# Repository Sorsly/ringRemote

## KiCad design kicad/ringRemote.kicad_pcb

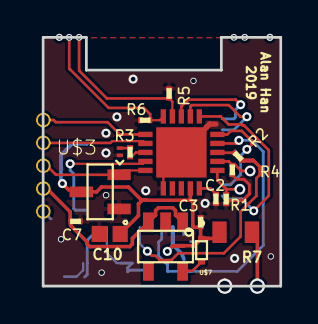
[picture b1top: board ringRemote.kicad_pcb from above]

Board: 4 copper layers, 13.2 x 13.8 mm, 23 parts (0 on the bottom side), 24 nets.

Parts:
C2, C3, C7: 1uF; 0201
C4: 0.1uF; 0201
C5, C6: 4pF; 0201
C9, C10: 10uF; 0402
D1: ORANGE; LED-0201
R1, R2, R3, R4, R5, R6: 100k; 0201
R7: 1.8k; 0805
U$1: MAX32660; T2044+5C
U$2: ATBTLC1000-ZR110CA
U$3: TPS3839G25; 3-SOT-23
U$4: TLV700; SOT-23-THIN
U$6: 1X5_1.27MM
U$7: DB2731400L; SSSMINI2
Y1: 32.768kHz; CRYSTAL-SMD-3.2X1.5MM

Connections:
+5V: C7.1, U$4.P$1, U$4.P$3, U$6.P$2
/AO_GPIO_0_WAKE: U$1.P$4, U$2.P$1
/BT_CTS: U$1.P$15, U$2.P$20
/BT_RTS: U$1.P$16, U$2.P$21
/BT_RXD: U$1.P$18, U$2.P$14
/BT_TXD: U$1.P$17, U$2.P$15
/CLKSRC: C6.1, U$2.P$33, Y1.P$1
/C_EN: R2.2, U$1.P$13
/MAXRST: U$1.P$5, U$3.P$2, U$6.P$3
/PB1: R1.1, U$1.P$11
/PB2: R4.1, U$1.P$12
/PB3: R5.1, U$1.P$19
/PB4: R6.1, U$1.P$20
/SWDCLK: U$1.P$1, U$6.P$5
/SWDIO: U$1.P$2, U$6.P$4
/WAKEMONITOR: U$1.P$14, U$2.P$28
GND: C2.2, C3.2, C4.2, C5.2, C6.2, C7.2, C9.2, C10.2, D1.C, R1.2, R4.2, R5.2, R6.2, U$1.P$0, U$1.P$6, U$2.P$11, U$2.P$26, U$2.P$35, U$3.P$1, U$4.P$2, U$6.P$1
unnamed: C2.1, U$1.P$10
unnamed: C5.1, U$2.P$34, Y1.P$2
unnamed: D1.A, R3.2
unnamed: R2.1, U$2.P$30
unnamed: R3.1, U$1.P$3
unnamed: U$4.P$5, U$7.P$2
VCC: C3.1, C4.1, C9.1, C10.1, R7.2, U$1.P$9, U$2.P$7, U$2.P$27, U$3.P$3, U$7.P$1

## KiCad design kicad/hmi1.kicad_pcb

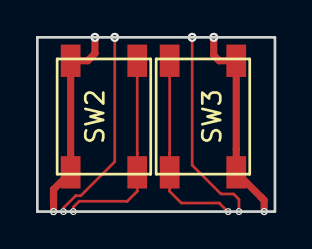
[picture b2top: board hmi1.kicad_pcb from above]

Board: 2 copper layers, 13.2 x 9.7 mm, 3 parts (0 on the bottom side), 3 nets.

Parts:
FRAME1: FRAME-LETTERNO_PACKAGE; DUMMY
SW2, SW3: SW_SPST_0; RS-187R05A2-DS MT RT

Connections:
/PB2: SW3.1, SW3.2
/PB3: SW2.1, SW2.2
VCC: SW2.3, SW2.4, SW3.3, SW3.4

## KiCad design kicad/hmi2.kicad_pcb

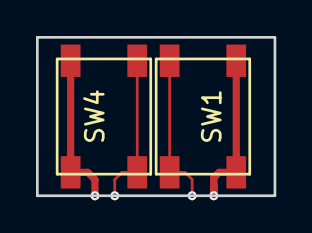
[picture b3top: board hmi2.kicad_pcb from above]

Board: 2 copper layers, 13.2 x 8.8 mm, 3 parts (0 on the bottom side), 3 nets.

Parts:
FRAME1: FRAME-LETTERNO_PACKAGE; DUMMY
SW1, SW4: SW_SPST_0; RS-187R05A2-DS MT RT

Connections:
/PB1: SW1.1, SW1.2
/PB4: SW4.1, SW4.2
VCC: SW1.3, SW1.4, SW4.3, SW4.4

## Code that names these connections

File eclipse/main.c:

/**
 * @file    main.c
 * @brief   Hello World!
 * @details This example uses the UART to print to a terminal and flashes an LED.
 */

/*******************************************************************************
 * Copyright (C) 2016 Maxim Integrated Products, Inc., All Rights Reserved.
 *
 * Permission is hereby granted, free of charge, to any person obtaining a
 * copy of this software and associated documentation files (the "Software"),
 * to deal in the Software without restriction, including without limitation
 * the rights to use, copy, modify, merge, publish, distribute, sub-license,
 * and/or sell copies of the Software, and to permit persons to whom the
 * Software is furnished to do so, subject to the following conditions:
 *
 * The above copyright notice and this permission notice shall be included
 * in all copies or substantial portions of the Software.
 *
 * THE SOFTWARE IS PROVIDED "AS IS", WITHOUT WARRANTY OF ANY KIND, EXPRESS
 * OR IMPLIED, INCLUDING BUT NOT LIMITED TO THE WARRANTIES OF
 * MERCHANTABILITY, FITNESS FOR A PARTICULAR PURPOSE AND NONINFRINGEMENT.
 * IN NO EVENT SHALL MAXIM INTEGRATED BE LIABLE FOR ANY CLAIM, DAMAGES
 * OR OTHER LIABILITY, WHETHER IN AN ACTION OF CONTRACT, TORT OR OTHERWISE,
 * ARISING FROM, OUT OF OR IN CONNECTION WITH THE SOFTWARE OR THE USE OR
 * OTHER DEALINGS IN THE SOFTWARE.
 *
 * Except as contained in this notice, the name of Maxim Integrated
 * Products, Inc. shall not be used except as stated in the Maxim Integrated
 * Products, Inc. Branding Policy.
 *
 * The mere transfer of this software does not imply any licenses
 * of trade secrets, proprietary technology, copyrights, patents,
 * trademarks, mask work rights, or any other form of intellectual
 * property whatsoever. Maxim Integrated Products, Inc. retains all
 * ownership rights.
 *
 * $Date: 2018-08-09 23:45:02 +0000 (Thursday, 09 August 2018) $
 * $Revision: 36818 $
 *
 ******************************************************************************/

/***** Includes *****/
#include <stdio.h>
#include <stdint.h>
#include <stdbool.h>

//delay libraries
#include "mxc_config.h"
#include "mxc_delay.h"

#include "tmr.h"
#include "tmr_utils.h"

//led library
#include "led.h"

//required libraries
#include "board.h"  //this NEEDS to be before gpio.h apparently
#include "gpio.h"


/***** Definitions *****/
//reminder that all pins listed here are SOFTWARE, not HARDWARE
#define PB1_PIN     PIN_9
#define PB2_PIN     PIN_8
#define PB3_PIN     PIN_3
#define PB4_PIN     PIN_2
#define THRESH      10      //ms
#define TMR0        MXC_TMR0

/***** Globals *****/

/***** Functions *****/

bool debounce(bool *prevSt, int *tStart, bool currSt) {
    if(currSt != *prevSt) {     //change has occured
        TMR_Enable(TMR0);       //enables timer on change
        *tStart = TMR_GetCount(TMR0);
        *prevSt = currSt;
    } else {
        if((TMR_GetCount(TMR0) - *tStart) > THRESH) {
            *prevSt = currSt;
            currSt = !currSt;
            TMR_Disable(TMR0);  //disables timer after settling
        }
    }

    return currSt;
}

void debounce(bool press) {
    if(press == true) {
        on++;   //count time up
        off = 0;
        if(on > THRESH) {
            if(output == false) {
                //action
                output = true;
            }
        }
    } else {
        off++;
        on = 0;
        if(off > THRESH) {
            output = 0;
            off = 0;
        }
    }
}

//inits atbtlc device
void btInit() {
    //TODO

}

//tells atbtlc to send bytes
void btTx(int byte) {
    //TODO
    
}

//timer interrupt
void gpio_isr(void *cbdata)
{
    //cbdata.ten = 1;   //enable timer
    TMR_Enable(TMR0);   //enable timer
}


int main(void)
{
//declarations
    gpio_cfg_t pb1, pb2, pb3, pb4;
    bool fx1 = false;
    bool fx2 = false;
    bool fx3 = false;
    bool fx4 = false;

    //int tElapsed;

    tmr_cfg_t tmr;

    btInit();

//MXC_TMR0 init config
    /*
    TMR0_CN.ten = 0;    //disable timer
    TMR0_CN.tmode = 000b;    //one-shot mode
    //TMR0_CN.pres3:TMR0_CN.pres    //set prescaler //TODO
    TMR0_CMP = 10;
    //use "TMR0_CN.ten = 1;" to enable timer
    */

    unsigned clk_shift = 0;
    uint64_t max_us;

    /* Find the proper clock shift for timer */
    do {
        max_us = (uint64_t)((0xFFFFFFFFUL / ((uint64_t)PeripheralClock >> clk_shift++)) * 1000000UL);
    } while (us > max_us);
    clk_shift--;

    TMR_Disable(TMR0);
    TMR_Init(TMR0, 0, 0);   //prescaler is second arg
    
    //ms to ticks
    uint32_t ticks; //ticks temp var
    TMR_GetTicks(TMR0, THRESH, TMR_UNIT_MILLISEC, &ticks);  //get ticks from ms
    
    //define tmr
    tmr.mode = TMR_MODE_ONESHOT;
    tmr.cmp_cnt = ticks;    //timer mode?
    tmr.pol = 0;    //compare register value in timer ticks. not used
    
    TMR_Config(TMR0, &tmr); //configure tmr as TMR0

    //use "TMR_Enable(TMR0);" to enable timer


//interrupt pin init (turn into function)TODO
    pb1.port = PORT_0;
    pb1.mask = PB1_PIN;
    pb1.pad = GPIO_PAD_PULL_DOWN;
    pb1.func = GPIO_FUNC_IN;
    GPIO_Config(&pb1);
    
    //GPIO_RegisterCallback(&pb1, gpio_isr, &tElapsed);
    //GPIO_RegisterCallback(&pb1, gpio_isr, &TMR0_CN);
    GPIO_RegisterCallback(&pb1, gpio_isr);
    
    GPIO_IntConfig(&pb1, GPIO_INT_EDGE, GPIO_INT_BOTH); //reads on falling and rising
    
    GPIO_IntEnable(&pb1);
    NVIC_EnableIRQ((IRQn_Type)MXC_GPIO_GET_IRQ(GPIO_PORT_INTERRUPT_IN));

    pb2.port = PORT_0;
    pb2.mask = PB2_PIN;
    pb2.pad = GPIO_PAD_PULL_DOWN;
    pb2.func = GPIO_FUNC_IN;

    pb3.port = PORT_0;
    pb3.mask = PB3_PIN;
    pb3.pad = GPIO_PAD_PULL_DOWN;
    pb3.func = GPIO_FUNC_IN;

    pb4.port = PORT_0;
    pb4.mask = PB4_PIN;
    pb4.pad = GPIO_PAD_PULL_DOWN;
    pb4.func = GPIO_FUNC_IN;

//loop
    while(1) {
        if(TMR_IntStatus(TMR0)) {   //check if TMR0 finished the cnt
            //somehow pass which switch got pushed to the bt func
            if(GPIO_InGet(&pb1)) {
                btTx(1);
            } else if(GPIO_InGet(&pb2)) {
                btTx(2);
            } else if(GPIO_InGet(&pb3)) {
                btTx(3);
            } else if(GPIO_InGet(&pb4)) {
                btTx(4);
            }

            //TMR_IntClear(TMR0);     //unnecessary because interrupt clears auto?
        }
        

        //old code, not oriented for interrupts
        /***
        //read pb1
        if (GPIO_InGet(&pb1)) {
            fx1 = true;
        } else {
            fx1 = false;
        }

        //read pb2
        if (GPIO_InGet(&pb2)) {
            fx2 = true;
        } else {
            fx2 = false;
        }

        //read pb3
        if (GPIO_InGet(&pb3)) {
            fx3 = true;
        } else {
            fx3 = false;
        }

        //read pb4
        if (GPIO_InGet(&pb4)) {
            fx4 = true;
        } else {
            fx4 = false;
        }

        if (fx1 || fx2 || fx3 || fx4) {
            LED_On(0);  //just for the evalboard?
        } else {
            LED_Off(0);
        }
        ***/
    }
}

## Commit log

2019-01-06 added a todo list; did some thinking for the HMI pushbuttons
2019-01-06 added to bom: battery supervisor, charging circuit components; put components on board space to estimate stuff
2019-01-06 moved some datasheets from local/proj
2019-01-06 added battery supervisor part, wired it up
2019-01-07 made a new sheet, moved all power stuff to second sheet; added charger circuit; added connector; added battery. pretty much just need to determine the programming interface before I start doing board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
2019-01-07 some models from octopart
2019-01-07 added pertinent datasheets, including programming stuff for MAX
2019-01-07 misc save
2019-01-14 made rough layout of board; swapped some pins for pushbuttons in sch (to atbtlc); understood programming workflow a bit better (likely using SWD instead of i2c)
2019-01-14 created mech directory
2019-01-16 think I moved the pb's back to MAX32660 (using the i2c lines because they're not needed)
2019-01-19 pretty much finished the board; swapped diode out for a smaller package
2019-01-21 tried to create some vias for the pushbuttons, these need to be routed offboard (past castellated edge near antenna section); created rev1 of mech model (this needs to be bigger and smoother, hurts m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
2019-01-22 moved eagle files to subdir
2019-01-22 some misc mech outputs
2019-01-22 switched over to kicad for 4-layer stuff
2019-01-22 switched over to kicad for 4-layer stuff
    *also fixed some clearance issues (set up some drc stuff)
    *wired out hmi traces towards antenna end
    *redefined board edge.cuts to suit custom shape better
2019-01-22 had to wire GND castellation to polypour; the border technically isn't filled
2019-01-23 finished routing main board; changed programming castellations to circular; created subschematic for battery board
2019-01-23 finished battery board; added switch footprint to library; need to make symbol for switch and make switch board
2019-01-24 added 4 pin spst switch and finished sch
2019-01-24 finished hmi boards
2019-01-24 added pdfs of to-scale layouts (for design review)
2019-01-24 misc stuff
2019-01-25 fixed MAX32660 footprint (was actually wrong, design reviews are good), updated to board; slightly nudged pb4 via away from pb3 via (drc error)
2019-01-25 misc fix
2019-01-25 fixed the pb4 issue on the hmi1 side; also cleared drc after fiddling with rules
2019-01-25 ran drc on hmi2 (is good, no resubmit necessary); slightly moved battery on battery, drc on battery is fine (resubmit though)
2019-01-25 updated pdfs; bottom had to be mirrored this time because I forgot to last time; top has updated footprint for max
2019-02-13 added initial c code for MAX32660
2019-02-17 changed some of how interrupts will work, etc.
2019-02-18 final commit for uncommon hacks, moving back to desktop
2019-02-18 mech changes from before uh2019
2019-02-18 moved code into a sub dir and added an eclipse workspace to save debug config; fixed compile errors
2019-02-18 modified btTx to pulse LED distinguishing each switch; test succeededgit status! next, need to verify if debouncing is working properly
2019-02-19 changed bttx led delays and added macro for led pin
2019-03-10 some stuff that shouldn't be tracked; cleaned up some of the old code in main.c (deleted stuff)
2019-03-10 added a bit of bt init code
2019-03-17 finished code for basic bt functionality; cleaned up some old code; need to find encryption support and implement low power operation
